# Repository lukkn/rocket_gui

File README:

# Communication between Teensy and MOTE board

## SETUP INSTRUNCTIONS
1. Connect each MoTE board used to 12V power, connecting to the 2 pins on J1 closest to the top of the board. Upper pin is power, lower pin is ground. Connect each teensy to the router via ethernet, and connect the control console to the same router
2. In the file "Example SD card Root/sensor_min_test.csv", add all necessary sensors and/or actuators, make sure to specify mote number, pin number, and sensor type (see below for sensor types). For ADCs, the pin number is weird. The first digit is the ADC number (counting from the left, starting at 0), and the second digit is the pin number. E.g. ADC pin number 11 is J20, pin 1. For 2ch ADCs, use a pin number of 0 for the left two pins and pin number 1 for the right two pins.
3. Once the teensy is powered and conneted, run gui.py, the orange status light on the teensy will be on if there is a connection. If you need to change any config informaiton, REBOOT THE TEENSY!!

## Sensor Types
* Teensy ADC
* i2c ADC 1ch
* i2c ADC 2ch
* servoPWM
* servoPWM_12V
* Binary GPIO

## Identifying each Teensy and MOTE Board

Each MOTE board will hold a teensy. We can identify each by their unique MOTE number.

They will be last digit of each MOTE's static IP. That digit will be saved as an ascii-value in MoteNumber.txt in SD card.

## Communication Protocol

Protocol used between Teensy and the GUI will be done in **UDP**.

## Types of Functions

There are 4 types of read functions for sensors and 2 types of write functions for actuators.

Each function is assigned an Interface Type Number.

**Read functions:**

1. Teensy ADC
2. i2c ADC 1 channel (ads122c4)
3. i2c ADC 2 channel (ads122c4) (for thermocouple)
4. flowmeter counter

**Write functions:**

5. servo PWM
6. binary gpio

| Operation | Interface Type Number | Sensor/Actuator                                 |
| --------- | --------------------- | ----------------------------------------------- |
| READ      | 1                     | Teensy ADC                                      |
| READ      | 2                     | I2C ADC 1 channel (ads122c4)                    |
| READ      | 3                     | I2C ADC 2 channel (ads122c4) (for thermocouple) |
| READ      | 4                     | Flowmeter Counter                               |
| WRITE     | 5                     | Servo PWM                                       |
| WRITE     | 6                     | Binary GPIO                                     |

## Packet Data Structure

Each packet will be sent and received as a **byte array**.

### Sensor Config Commands (Server -> Teensy):

**Byte Array**

| Byte 1  | Byte 2      |
| ------- | ----------- |
| pin_num | config_byte |

**Bit Array of `config_byte`**

| Bit 1 (MSB)                                                              | Bit 2                                              | Bit 3 - 8             |
| ------------------------------------------------------------------------ | -------------------------------------------------- | --------------------- |
| actuator write command = 0 (since this is not an actuator write command) | actuator state (not used in sensor config packets) | Interface Type Number |

**NB 1.** Byte variable can be of type `char` or `uint8` or `hex` as its eight bits long.

**NB 2.** Given we are dealing with sensors, _Interface Type Number_ is either 1, 2, or 3, and _Bit 1_ and _Bit 2_ are 0.

**NB 3.** Knowing the pin number and sensor type is enough info to call the correct sensor read function, which takes pin number as argument.

### Actuator Write Commands (Server -> Teensy):

**Byte Array**

| Byte 1  | Byte 2      |
| ------- | ----------- |
| pin_num | config_byte |

**Bit Array of `config_byte`**

| Bit 1 (MSB)                                                            | Bit 2          | Bit 3 - 8             |
| ---------------------------------------------------------------------- | -------------- | --------------------- |
| Actuator write command = 1 (because this is an actuator write command) | actuator state | Interface Type Number |

**NB 4.** Given we are dealing with actuators, _Interface Type Number_ is either 4 or 5.

### Sensor Data (Teensy -> Server)

The byte array ar however many sensors there are in each teensy, whose information is provided in config file

Each Teensy will send to the server a differently lengthed byte array.

**Byte Array**

| Byte 1              | Byte 2-5               | Byte 6              | Byte 7-10              | etc. (5 bytes per sensor: 1 pin byte, 4 data bytes) |
| ------------------- | ---------------------- | ------------------- | ---------------------- | --------------------------------------------------- |
| pin_num of sensor_1 | data_value of sensor_1 | pin_num of sensor_2 | data_value of sensor_2 | Pin & dava_val of sensors_3-to-n                    |

**NB 5.** _data_value_ for each sensor is an int (4 bytes).

# To compile Teensy code from command line (without Arduino IDE). NOT USED FOR CURRENT CODE

If cloning this repo to compile firmware, you need to run the following once (to download the teensy4 core):

```
git submodule init
git submodule update
```

To update submodules:

```
git submodule foreach git pull

dependencies:
arm-none-eabi-newlib
arm-none-eabi-gcc
```

The PWMServo library is modified to INVERT the PWM duty cycle because we're using a MOSFET to drive a higher voltage, which inverts the signal
line 198 of PMWServo.cpp

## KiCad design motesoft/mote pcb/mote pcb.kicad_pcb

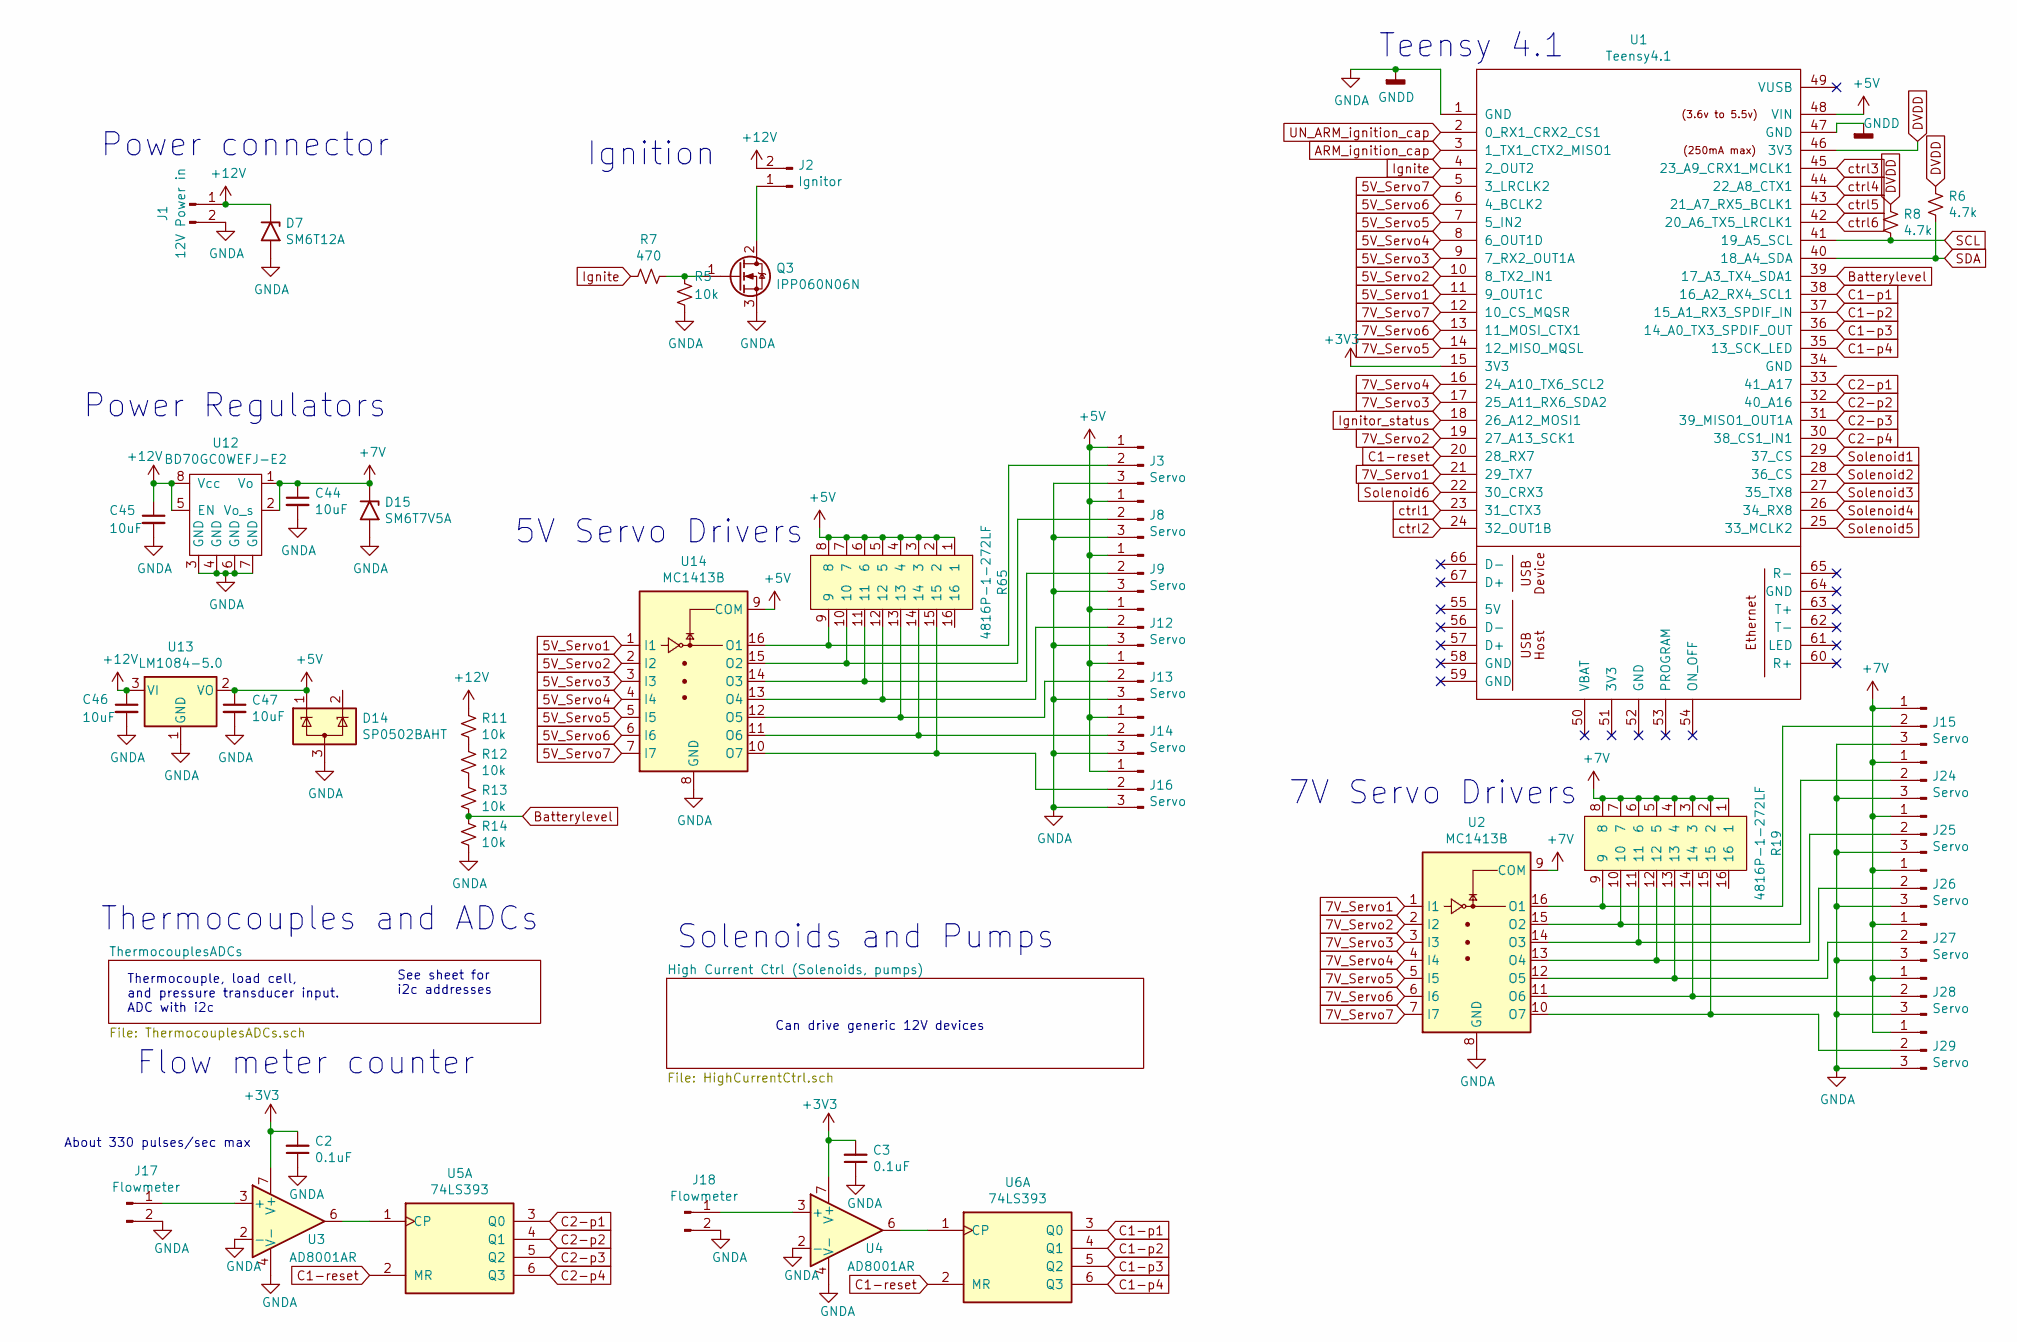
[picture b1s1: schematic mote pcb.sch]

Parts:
C2, C3: 0.1uF; C_0603_1608Metric_Pad1.08x0.95mm_HandSolder; LCSC Part # C14663
C44, C45, C46, C47: 10uF; C_0603_1608Metric_Pad1.08x0.95mm_HandSolder; LCSC Part # C19702
D7: SM6T12A; D_SMB
D14: SP0502BAHT; SOT-23
D15: SM6T7V5A; D_SMB
J1: 12V Power in; JST_EH_B4B-EH-A_1x04_P2.50mm_Vertical
J2: Ignitor; JST_EH_B4B-EH-A_1x04_P2.50mm_Vertical
J3, J8, J9, J12, J13, J14, J15, J16, J24, J25, J26, J27, J28, J29: Servo; JST_EH_B4B-EH-A_1x04_P2.50mm_Vertical
J17, J18: Flowmeter; JST_EH_B4B-EH-A_1x04_P2.50mm_Vertical
Q3: IPP060N06N; TO-220-3_Vertical
R5, R11, R12, R13, R14: 10k; R_0603_1608Metric_Pad0.98x0.95mm_HandSolder; LCSC Part # C25804
R6, R8: 4.7k; R_0603_1608Metric_Pad0.98x0.95mm_HandSolder; LCSC Part # C23162
R7: 470; R_0603_1608Metric_Pad0.98x0.95mm_HandSolder; LCSC Part # C23179
R19, R65: 4816P-1-272LF; SOIC-16W_5.3x10.2mm_P1.27mm
U1: Teensy4.1; Teensy41
U2, U14: MC1413B; SOIC-16_3.9x9.9mm_P1.27mm
U3, U4: AD8001AR; SOIC-8_3.9x4.9mm_P1.27mm
U5, U6: 74LS393; SOIC-14_3.9x8.7mm_P1.27mm
U12: BD70GC0WEFJ-E2; SOIC-8-1EP_3.9x4.9mm_P1.27mm_EP2.29x3mm_ThermalVias
U13: LM1084-5.0; TO-263-3_TabPin2

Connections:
5V_Servo1: U1.11 (9_OUT1C), U14.1 (I1)
5V_Servo2: U1.10 (8_TX2_IN1), U14.2 (I2)
5V_Servo3: U1.9 (7_RX2_OUT1A), U14.3 (I3)
5V_Servo4: U1.8 (6_OUT1D), U14.4 (I4)
5V_Servo5: U1.7 (5_IN2), U14.5 (I5)
5V_Servo6: U1.6 (4_BCLK2), U14.6 (I6)
5V_Servo7: U1.5 (3_LRCLK2), U14.7 (I7)
7V_Servo1: U1.21 (29_TX7), U2.1 (I1)
7V_Servo2: U1.19 (27_A13_SCK1), U2.2 (I2)
7V_Servo3: U1.17 (25_A11_RX6_SDA2), U2.3 (I3)
7V_Servo4: U1.16 (24_A10_TX6_SCL2), U2.4 (I4)
7V_Servo5: U1.14 (12_MISO_MQSL), U2.5 (I5)
7V_Servo6: U1.13 (11_MOSI_CTX1), U2.6 (I6)
7V_Servo7: U1.12 (10_CS_MQSR), U2.7 (I7)
+3V3: C2.2, C3.2, U1.15 (3V3), U3.7 (V+), U4.7 (V+); also elsewhere on the board
+5V: C47.1, D14.1 (K), J3.1, J8.1, J9.1, J12.1, J13.1, J14.1, J16.1, R65.1, R65.2, R65.3, R65.4, R65.5, R65.6, R65.7, R65.8, U1.48 (VIN), U13.2 (VO), U14.9 (COM)
+7.5V: C44.1, D15.1 (A1), J15.1, J24.1, J25.1, J26.1, J27.1, J28.1, J29.1, R19.1, R19.2, R19.3, R19.4, R19.5, R19.6, R19.7, R19.8, U2.9 (COM), U12.1 (Vo), U12.2 (Vo_s)
+12V: C45.1, C46.1, D7.1 (A1), J1.1, J2.2, R11.1, U12.5 (EN), U12.8 (Vcc), U13.3 (VI); also elsewhere on the board
Batterylevel: R13.2, R14.1, U1.39 (17_A3_TX4_SDA1)
C1-p1: U1.38 (16_A2_RX4_SCL1), U6.3 (Q0)
C1-p2: U1.37 (15_A1_RX3_SPDIF_IN), U6.4 (Q1)
C1-p3: U1.36 (14_A0_TX3_SPDIF_OUT), U6.5 (Q2)
C1-p4: U1.35 (13_SCK_LED), U6.6 (Q3)
C1-reset: U1.20 (28_RX7), U5.2 (MR), U6.2 (MR)
C2-p1: U1.33 (41_A17), U5.3 (Q0)
C2-p2: U1.32 (40_A16), U5.4 (Q1)
C2-p3: U1.31 (39_MISO1_OUT1A), U5.5 (Q2)
C2-p4: U1.30 (38_CS1_IN1), U5.6 (Q3)
DVDD: R6.1, R8.1, U1.46 (3V3)
GNDA: C2.1, C3.1, C44.2, C45.2, C46.2, C47.2, D7.2 (A2), D14.3 (A), D15.2 (A2), J1.2, J3.3, J8.3, J9.3, J12.3, J13.3, J14.3, J15.3, J16.3, J17.2, J18.2, J24.3, J25.3, J26.3, J27.3, J28.3, J29.3, Q3.3 (S), R5.2, R14.2, U1.1 (GND), U1.47 (GND), U2.8 (GND), U3.2 (-), U3.4 (V-), U4.2 (-), U4.4 (V-), U12.3 (GND), U12.4 (GND), U12.6 (GND), U12.7 (GND), U13.1 (GND), U14.8 (GND); also elsewhere on the board
Ignite: R7.2, U1.4 (2_OUT2)
unnamed: J2.1, Q3.2 (D)
unnamed: J3.2, R65.9, U14.16 (O1)
unnamed: J8.2, R65.10, U14.15 (O2)
unnamed: J9.2, R65.11, U14.14 (O3)
unnamed: J12.2, R65.12, U14.13 (O4)
unnamed: J13.2, R65.13, U14.12 (O5)
unnamed: J14.2, R65.14, U14.11 (O6)
unnamed: J15.2, R19.9, U2.16 (O1)
unnamed: J16.2, R65.15, U14.10 (O7)
unnamed: J17.1, U3.3 (+)
unnamed: J18.1, U4.3 (+)
unnamed: J24.2, R19.10, U2.15 (O2)
unnamed: J25.2, R19.11, U2.14 (O3)
unnamed: J26.2, R19.12, U2.13 (O4)
unnamed: J27.2, R19.13, U2.12 (O5)
unnamed: J28.2, R19.14, U2.11 (O6)
unnamed: J29.2, R19.15, U2.10 (O7)
unnamed: Q3.1 (G), R5.1, R7.1
unnamed: R11.2, R12.1
unnamed: R12.2, R13.1
unnamed: U3.6, U5.1 (CP)
unnamed: U4.6, U6.1 (CP)
SCL: R8.2, U1.41 (19_A5_SCL); also elsewhere on the board
SDA: R6.2, U1.40 (18_A4_SDA); also elsewhere on the board
Solenoid1: U1.29 (37_CS); also elsewhere on the board
Solenoid2: U1.28 (36_CS); also elsewhere on the board
Solenoid3: U1.27 (35_TX8); also elsewhere on the board
Solenoid4: U1.26 (34_RX8); also elsewhere on the board
Solenoid5: U1.25 (33_MCLK2); also elsewhere on the board
Solenoid6: U1.22 (30_CRX3); also elsewhere on the board
ctrl1: U1.23 (31_CTX3); also elsewhere on the board
ctrl2: U1.24 (32_OUT1B); also elsewhere on the board
ctrl3: U1.45 (23_A9_CRX1_MCLK1); also elsewhere on the board
ctrl4: U1.44 (22_A8_CTX1); also elsewhere on the board
ctrl5: U1.43 (21_A7_RX5_BCLK1); also elsewhere on the board
ctrl6: U1.42 (20_A6_TX5_LRCLK1); also elsewhere on the board

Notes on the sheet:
Thermocouple, load cell, and pressure transducer input. ADC with i2c
See sheet for i2c addresses
Ignition
Thermocouples and ADCs
Flow meter counter
Teensy 4.1
About 330 pulses/sec max
Power connector
7V Servo Drivers
Can drive generic 12V devices
Solenoids and Pumps
5V Servo Drivers
Power Regulators

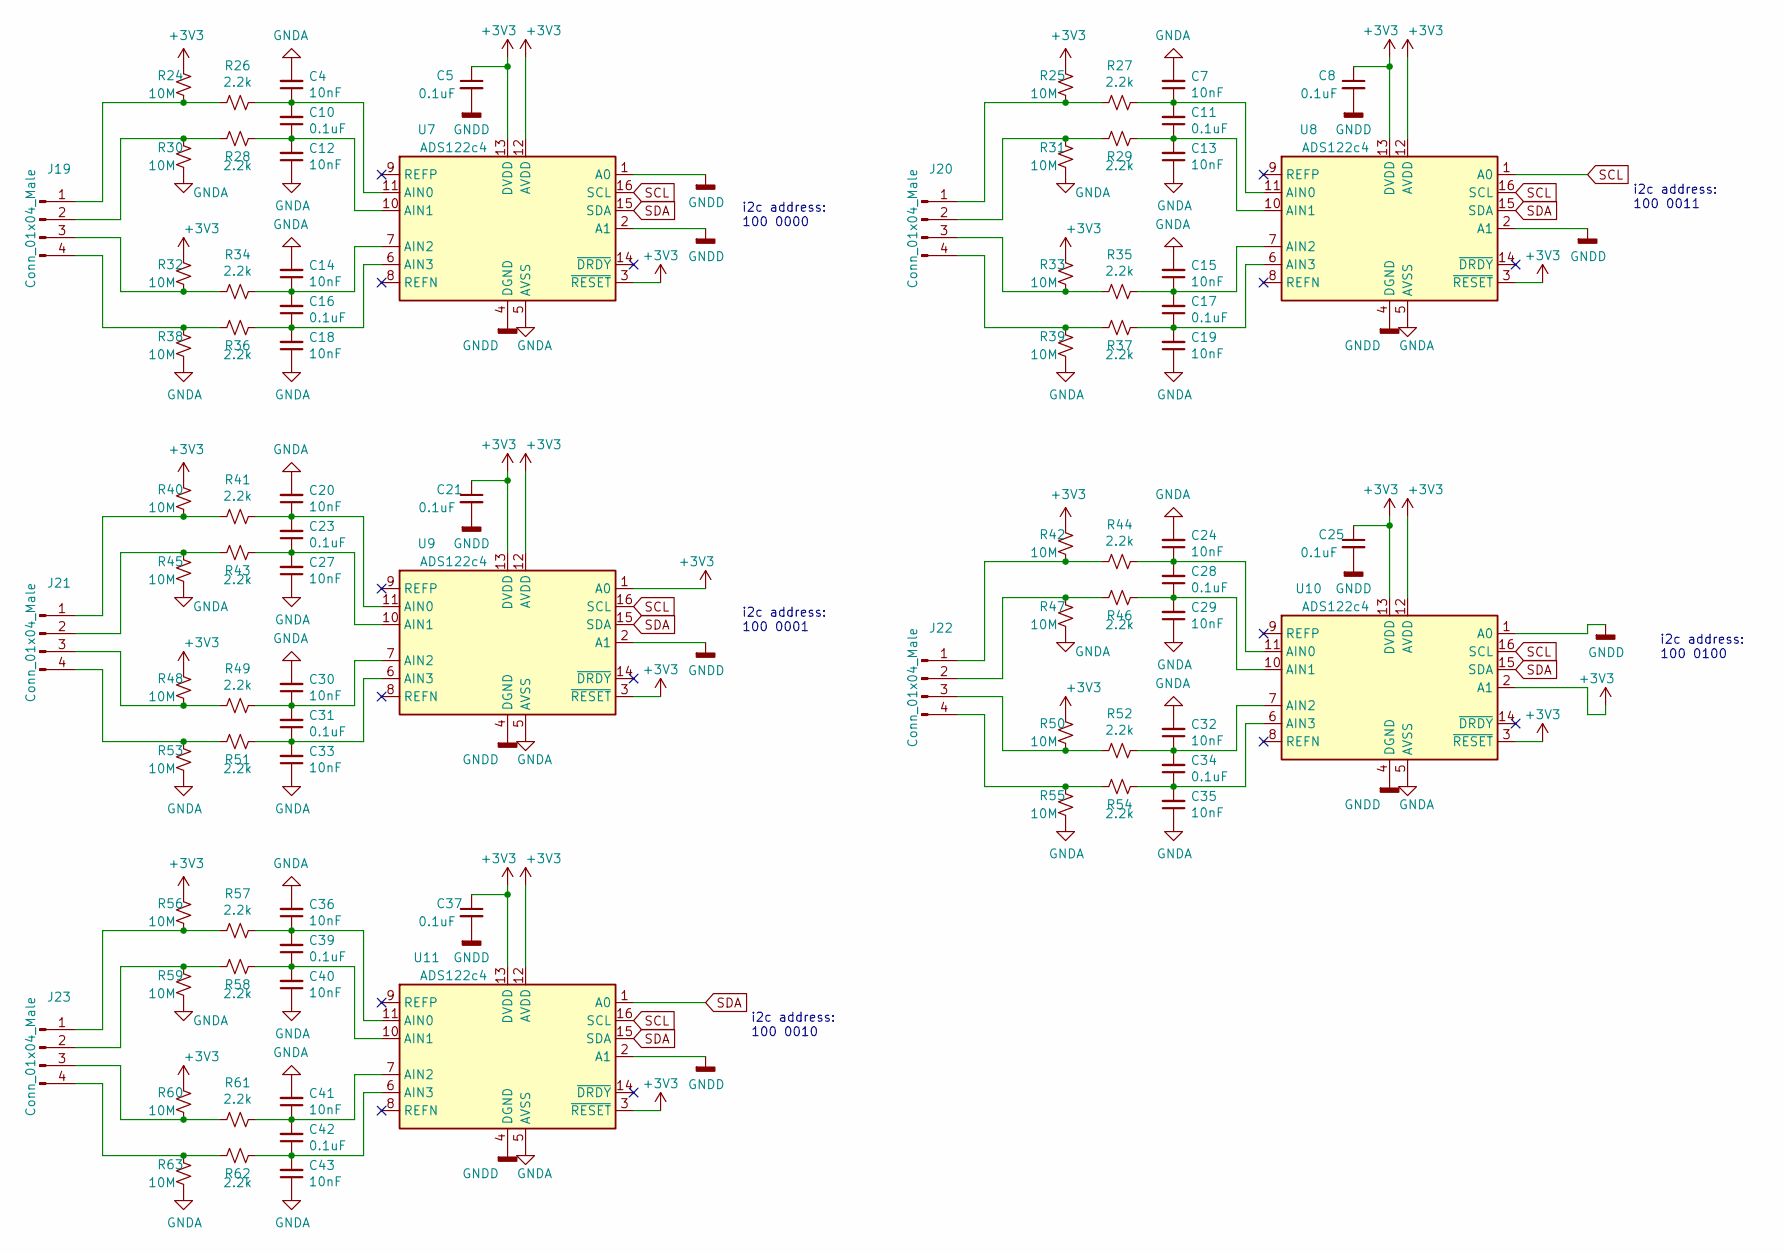
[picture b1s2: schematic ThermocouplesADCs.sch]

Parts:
C4, C7, C12, C13, C14, C15, C18, C19, C20, C24, C27, C29, C30, C32, C33, C35, C36, C40, C41, C43: 10nF; C_0603_1608Metric_Pad1.08x0.95mm_HandSolder; LCSC Part # C57112
C5, C8, C10, C11, C16, C17, C21, C23, C25, C28, C31, C34, C37, C39, C42: 0.1uF; C_0603_1608Metric_Pad1.08x0.95mm_HandSolder; LCSC Part # C14663
J19, J20, J21, J22, J23: Conn_01x04_Male; JST_EH_B4B-EH-A_1x04_P2.50mm_Vertical
R24, R25, R30, R31, R32, R33, R38, R39, R40, R42, R45, R47, R48, R50, R53, R55, R56, R59, R60, R63: 10M; R_0603_1608Metric_Pad0.98x0.95mm_HandSolder; LCSC Part # C7250
R26, R27, R28, R29, R34, R35, R36, R37, R41, R43, R44, R46, R49, R51, R52, R54, R57, R58, R61, R62: 2.2k; R_0603_1608Metric_Pad0.98x0.95mm_HandSolder; LCSC Part # C4190
U7, U8, U9, U10, U11: ADS122c4; TSSOP-16_4.4x5mm_P0.65mm

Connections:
+3V3: C5.1, C8.1, C21.1, C25.1, C37.1, R24.2, R25.2, R32.2, R33.2, R40.2, R42.2, R48.2, R50.2, R56.2, R60.2, U7.3 (~RESET), U7.12 (AVDD), U7.13 (DVDD), U8.3 (~RESET), U8.12 (AVDD), U8.13 (DVDD), U9.1 (A0), U9.3 (~RESET), U9.12 (AVDD), U9.13 (DVDD), U10.2 (A1), U10.3 (~RESET), U10.12 (AVDD), U10.13 (DVDD), U11.3 (~RESET), U11.12 (AVDD), U11.13 (DVDD); also elsewhere on the board
GNDA: C4.2, C5.2, C7.2, C8.2, C12.1, C13.1, C14.2, C15.2, C18.1, C19.1, C20.2, C21.2, C24.2, C25.2, C27.1, C29.1, C30.2, C32.2, C33.1, C35.1, C36.2, C37.2, C40.1, C41.2, C43.1, R30.1, R31.1, R38.1, R39.1, R45.1, R47.1, R53.1, R55.1, R59.1, R63.1, U7.1 (A0), U7.2 (A1), U7.4 (DGND), U7.5 (AVSS), U8.2 (A1), U8.4 (DGND), U8.5 (AVSS), U9.2 (A1), U9.4 (DGND), U9.5 (AVSS), U10.1 (A0), U10.4 (DGND), U10.5 (AVSS), U11.2 (A1), U11.4 (DGND), U11.5 (AVSS); also elsewhere on the board
unnamed: C10.1, C12.2, R28.2, U7.10 (AIN1)
unnamed: C4.1, C10.2, R26.2, U7.11 (AIN0)
unnamed: C11.1, C13.2, R29.2, U8.10 (AIN1)
unnamed: C7.1, C11.2, R27.2, U8.11 (AIN0)
unnamed: C14.1, C16.2, R34.2, U7.7 (AIN2)
unnamed: C15.1, C17.2, R35.2, U8.7 (AIN2)
unnamed: C16.1, C18.2, R36.2, U7.6 (AIN3)
unnamed: C17.1, C19.2, R37.2, U8.6 (AIN3)
unnamed: C20.1, C23.2, R41.2, U9.11 (AIN0)
unnamed: C23.1, C27.2, R43.2, U9.10 (AIN1)
unnamed: C24.1, C28.2, R44.2, U10.11 (AIN0)
unnamed: C28.1, C29.2, R46.2, U10.10 (AIN1)
unnamed: C30.1, C31.2, R49.2, U9.7 (AIN2)
unnamed: C31.1, C33.2, R51.2, U9.6 (AIN3)
unnamed: C32.1, C34.2, R52.2, U10.7 (AIN2)
unnamed: C34.1, C35.2, R54.2, U10.6 (AIN3)
unnamed: C36.1, C39.2, R57.2, U11.11 (AIN0)
unnamed: C39.1, C40.2, R58.2, U11.10 (AIN1)
unnamed: C41.1, C42.2, R61.2, U11.7 (AIN2)
unnamed: C42.1, C43.2, R62.2, U11.6 (AIN3)
unnamed: J19.1, R24.1, R26.1
unnamed: J19.2, R28.1, R30.2
unnamed: J19.3, R32.1, R34.1
unnamed: J19.4, R36.1, R38.2
unnamed: J20.1, R25.1, R27.1
unnamed: J20.2, R29.1, R31.2
unnamed: J20.3, R33.1, R35.1
unnamed: J20.4, R37.1, R39.2
unnamed: J21.1, R40.1, R41.1
unnamed: J21.2, R43.1, R45.2
unnamed: J21.3, R48.1, R49.1
unnamed: J21.4, R51.1, R53.2
unnamed: J22.1, R42.1, R44.1
unnamed: J22.2, R46.1, R47.2
unnamed: J22.3, R50.1, R52.1
unnamed: J22.4, R54.1, R55.2
unnamed: J23.1, R56.1, R57.1
unnamed: J23.2, R58.1, R59.2
unnamed: J23.3, R60.1, R61.1
unnamed: J23.4, R62.1, R63.2
SCL: U7.16 (SCL), U8.1 (A0), U8.16 (SCL), U9.16 (SCL), U10.16 (SCL), U11.16 (SCL); also elsewhere on the board
SDA: U7.15 (SDA), U8.15 (SDA), U9.15 (SDA), U10.15 (SDA), U11.1 (A0), U11.15 (SDA); also elsewhere on the board

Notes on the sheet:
i2c address: 100 0000
i2c address: 100 0001
i2c address: 100 0010
i2c address: 100 0011
i2c address: 100 0100

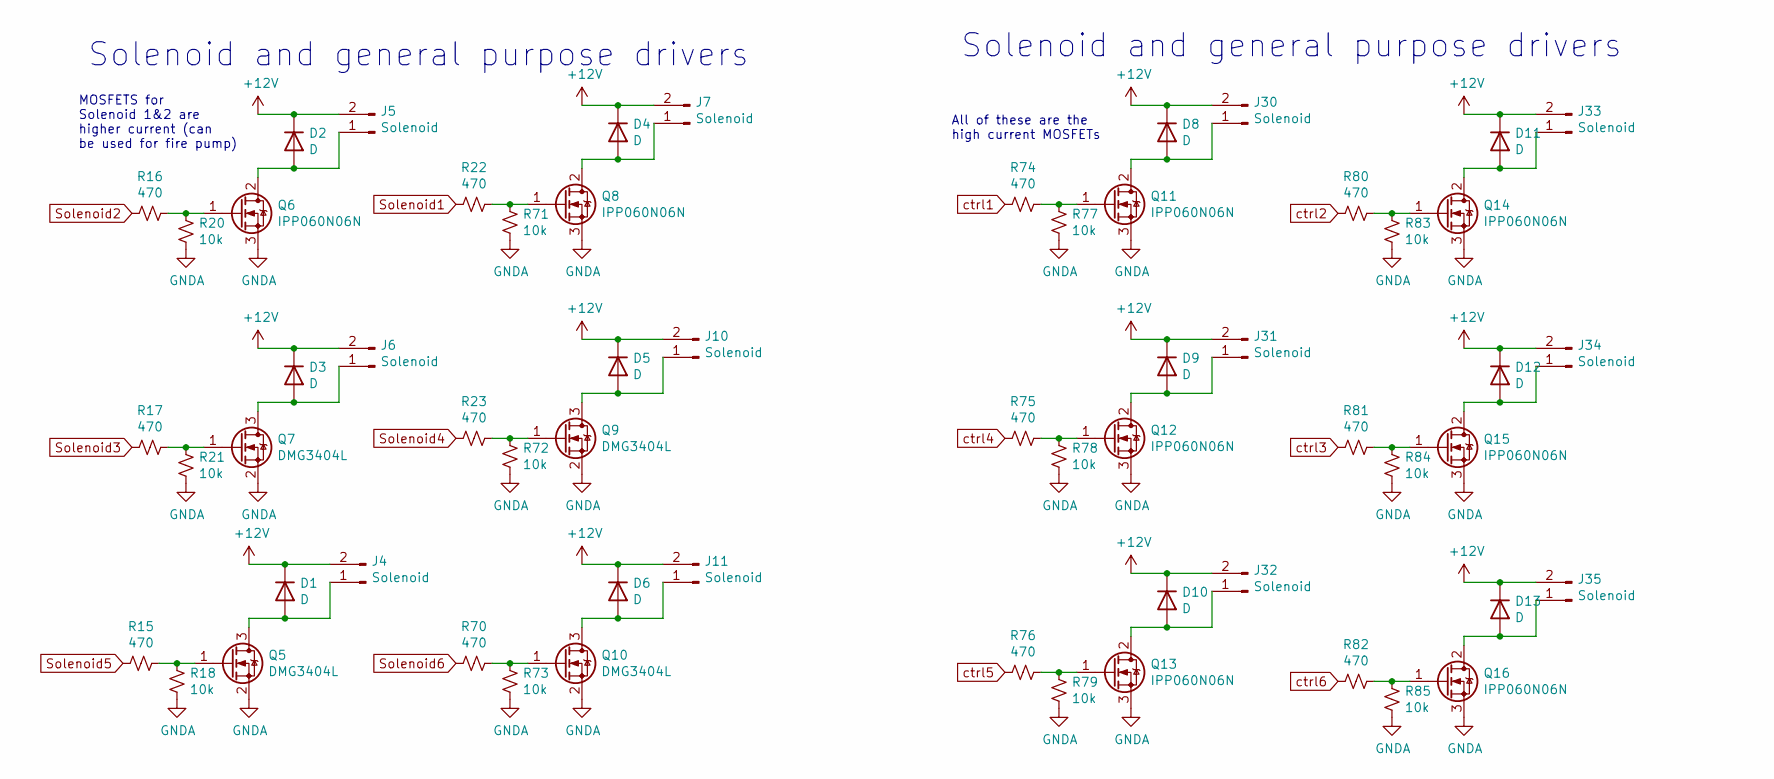
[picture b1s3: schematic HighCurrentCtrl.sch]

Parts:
D1, D2, D3, D4, D5, D6, D8, D9, D10, D11, D12, D13: D; D_SOD-123; LCSC Part # C8598
J4, J5, J6, J7, J10, J11, J30, J31, J32, J33, J34, J35: Solenoid; JST_EH_B4B-EH-A_1x04_P2.50mm_Vertical
Q5, Q7, Q9, Q10: DMG3404L; SOT-23
Q6, Q8, Q11, Q12, Q13, Q14, Q15, Q16: IPP060N06N; TO-220-3_Vertical
R15, R16, R17, R22, R23, R70, R74, R75, R76, R80, R81, R82: 470; R_0603_1608Metric_Pad0.98x0.95mm_HandSolder; LCSC Part # C23179
R18, R20, R21, R71, R72, R73, R77, R78, R79, R83, R84, R85: 10k; R_0603_1608Metric_Pad0.98x0.95mm_HandSolder; LCSC Part # C25804

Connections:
+12V: D1.1 (K), D2.1 (K), D3.1 (K), D4.1 (K), D5.1 (K), D6.1 (K), D8.1 (K), D9.1 (K), D10.1 (K), D11.1 (K), D12.1 (K), D13.1 (K), J4.2, J5.2, J6.2, J7.2, J10.2, J11.2, J30.2, J31.2, J32.2, J33.2, J34.2, J35.2; also elsewhere on the board
GNDA: Q5.2 (S), Q6.3 (S), Q7.2 (S), Q8.3 (S), Q9.2 (S), Q10.2 (S), Q11.3 (S), Q12.3 (S), Q13.3 (S), Q14.3 (S), Q15.3 (S), Q16.3 (S), R18.2, R20.2, R21.2, R71.2, R72.2, R73.2, R77.2, R78.2, R79.2, R83.2, R84.2, R85.2; also elsewhere on the board
unnamed: D1.2 (A), J4.1, Q5.3 (D)
unnamed: D2.2 (A), J5.1, Q6.2 (D)
unnamed: D3.2 (A), J6.1, Q7.3 (D)
unnamed: D4.2 (A), J7.1, Q8.2 (D)
unnamed: D5.2 (A), J10.1, Q9.3 (D)
unnamed: D6.2 (A), J11.1, Q10.3 (D)
unnamed: D8.2 (A), J30.1, Q11.2 (D)
unnamed: D9.2 (A), J31.1, Q12.2 (D)
unnamed: D10.2 (A), J32.1, Q13.2 (D)
unnamed: D11.2 (A), J33.1, Q14.2 (D)
unnamed: D12.2 (A), J34.1, Q15.2 (D)
unnamed: D13.2 (A), J35.1, Q16.2 (D)
unnamed: Q5.1 (G), R15.1, R18.1
unnamed: Q6.1 (G), R16.1, R20.1
unnamed: Q7.1 (G), R17.1, R21.1
unnamed: Q8.1 (G), R22.1, R71.1
unnamed: Q9.1 (G), R23.1, R72.1
unnamed: Q10.1 (G), R70.1, R73.1
unnamed: Q11.1 (G), R74.1, R77.1
unnamed: Q12.1 (G), R75.1, R78.1
unnamed: Q13.1 (G), R76.1, R79.1
unnamed: Q14.1 (G), R80.1, R83.1
unnamed: Q15.1 (G), R81.1, R84.1
unnamed: Q16.1 (G), R82.1, R85.1
Solenoid1: R22.2; also elsewhere on the board
Solenoid2: R16.2; also elsewhere on the board
Solenoid3: R17.2; also elsewhere on the board
Solenoid4: R23.2; also elsewhere on the board
Solenoid5: R15.2; also elsewhere on the board
Solenoid6: R70.2; also elsewhere on the board
ctrl1: R74.2; also elsewhere on the board
ctrl2: R80.2; also elsewhere on the board
ctrl3: R81.2; also elsewhere on the board
ctrl4: R75.2; also elsewhere on the board
ctrl5: R76.2; also elsewhere on the board
ctrl6: R82.2; also elsewhere on the board

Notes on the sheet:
MOSFETS for Solenoid 1&2 are higher current (can be used for fire pump)
Solenoid and general purpose drivers
All of these are the high current MOSFETs

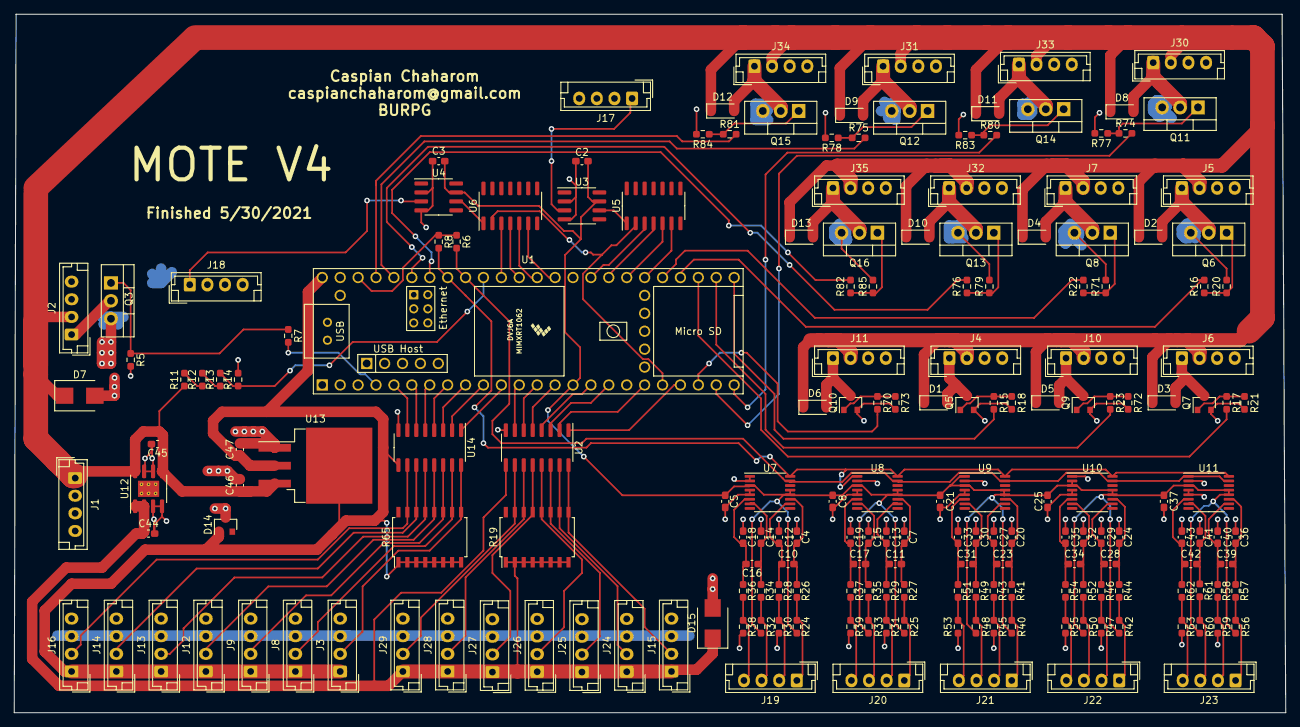
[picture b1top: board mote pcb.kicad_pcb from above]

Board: 2 copper layers, 180.3 x 99.1 mm, 192 parts (0 on the bottom side), 131 nets.

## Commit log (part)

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2023-12-26 requirements and folder refactor
2023-12-27 flask gui
2023-12-27 code cleanup
2023-12-27 button attempt
2023-12-27 better buttons
2023-12-27 button shit
2023-12-27 Placed buttons inside container
    - cleaned up repeated code
2023-12-27 update names
2023-12-27 Revert "better buttons"
    This reverts commit 9b7cf012b878d2701775844e0bdb4d0b0a95b217.
2023-12-27 Made buttons unselectable
    *spackle* sparkle
2023-12-27 Fixed unable to submit coordinates
    file was opened as read only
2023-12-27 fixed on/off buttons
    -changed buttons to div
2023-12-27 smaller buttons for actuators
2023-12-27 implemented collapsible menu
2023-12-27 Updated menu
2023-12-27 25px offset for menu bar and button status
2023-12-27 all actuators turned off on page load, other small changes
2023-12-27 button config almost correct overlay
2023-12-28 Made toggle buttons
    ... that I now have to remove
2023-12-28 Resolved conflicts
2023-12-28 Updated buttons to not toggle :(
2023-12-28 deleted useless files
2023-12-28 starting websocket conversion, much to do
2023-12-28 example web socket recieve shit
2023-12-28 example flask websocket
2023-12-28 Created sensor page that receives data from socket
2023-12-28 moved over to websocket for actuators.html page, need websocket for / and /loadconfig
2023-12-28 really rough sensors page
2024-01-01 dictionary parsing for config file with checks
2024-01-01 dictionary parsing for sensors page and id update
2024-01-02 sensor tare response, standardize response, hardcoded config
2024-01-02 renamed global variable sensors to sensor_list to avoid conflicts with html get function 'sensors' when using hardcoded dummy data
2024-01-02 tare buttons
2024-01-02 Created live graph
2024-01-02 Updated data frequency and improved performance
2024-01-02 local library for Chart.js
2024-01-02 sensors page uses local lib for Chart.js
2024-01-02 loggs data and emits data at different frequencies
2024-01-03 sensors on p&id view page, seperate table style pages for sensors and actuators
2024-01-03 renamed p&idview to pidview
2024-01-03 part of renaming
2024-01-03 added arm/disarm button
2024-01-03 Added graph toggle
    - checkbox for each sensor, graph appears when checked
2024-01-03 work in progress
2024-01-04 work in progress on main page
2024-01-04 Resized graphs
2024-01-04 Updated sensor page layout
2024-01-04 new graphs please
2024-01-04 Fixed graph appearance
2024-01-05 created js native graph on loadconfig page
2024-01-05 custom graph testing
2024-01-05 Created makeChart library
2024-01-05 Added add empty chart functionality
2024-01-06 performance tests and websocket lag fixed
2024-01-06 two lines on a graph example
2024-01-07 button presses and states are processed server side and ping added
2024-01-08 Added file upload/submit messages
2024-01-08 ping and app startup behavior change
2024-01-08 arm/disarm button now uses sockets instead of POST, no longer sending timestamps
2024-01-08 minor changes since last commit
2024-01-08 Implemented charts that plot lines when checkbox checked
    - still needs y-axis scale
    - still needs labelled/colored lines
2024-01-08 Fixed data duplication bug
    - if two or more charts were plotting the same sensor data updates were done multiple times
2024-01-09 bug fixes
2024-01-09 sync sensors
2024-01-09 gpt code that might be useful for queue management in constant time
2024-01-09 added different line colors
2024-01-09 testing and small changes, timer added to sensors
2024-01-09 Added grid lines
2024-01-09 Fixed graph data alignment on x-axis
2024-01-09 graph testing
2024-01-09 removed redundant imports
2024-01-09 created doubly linked list class
2024-01-09 Updated data storage to linkedlist
2024-01-09 updated defineScale for better performance
2024-01-09 test data for linked list
2024-01-09 test data for 3rd trial with linked list
2024-01-09 4th test using normal list
2024-01-10 deleted obsolete Chart.js file
2024-01-10 Removed extraneous files
2024-01-10 Revert to array data storage
2024-01-11 Created autosequence page
    - displays submitted csv file
2024-01-11 Update autosequence page layout
2024-01-11 Update autosequence style
2024-01-11 data points is param of updateData function, more colors and colors rotate if all used, some var types changed to let or const types
2024-01-11 removed unused imports
2024-01-11 config button uploads config, sig figs updated on sensors page and graphs
2024-01-11 Implemented autosequence backend and response
2024-01-12 Added stop timer function
2024-01-12 Updated launch to check for config, added cancel response
2024-01-12 Prevent relaunching after cancel without reuploading file
2024-01-12 minor changes
2024-01-13 renamed received_actuator_button_press socket to received_button_press
2024-01-13 dependencies in project folder, standardization of variable names, comments
    flask and flask-socketio are added into a folder. now a computer only needs python to run this gui
2024-01-13 updated .gitignore file
2024-01-13 deleted pycache
2024-01-14 production server eventlet used
2024-01-18 added autosequence page button to start page
2024-01-19 changed port to 5001 so it might work with macOS
2024-01-30 require gtk3
2024-01-30 require gtk3 sensor_logging
2024-01-30 Sensor_logging require gtk3
2024-01-30 Fixed bug where directory did not exist
2024-02-07 networking reqs
2024-02-09 Created networking skeleton
2024-02-09 rolled back python_flask_and_flaskio_and_eventlet_libraries folder
2024-02-09 Fixed networking errors
2024-02-09 autoseq actuators synced with other pages, boolean value in python prevents double clicks of launch button, pages update sensors+actuators on config upload, when disarmed sensor buttons can be clicke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
2024-02-09 send actuators commands to mote on button press
2024-02-09 minor import changes
2024-02-09 small import changes
2024-02-09 copy of socket at this moment
2024-02-09 changed 'button' to 'actuator'
2024-02-09 .gitignore update
2024-02-10 removed __pycache__ files
2024-02-10 .gitignore with every __pycache__
2024-02-10 autoseq changes and server change
2024-02-11 Style changes on home page (WIP)
2024-02-11 added telemetry receiver
2024-02-11 library and autoseq changes
2024-02-11 autoseq timing changes
2024-02-11 updated redline file
2024-02-11 tims changes
2024-02-11 added sensor data example
2024-02-12 new config and TODO
2024-02-12 slightly poked code
2024-02-12 Updated home page
2024-02-12 parse sensor data into frontend
2024-02-12 amended sensor data parsing
2024-02-12 fixed mote id in sensor telemetry
2024-02-13 modified MoTE firmware
2024-02-13 modified so we don't need sd card, reads as MoTE1
2024-02-13 dummy name for the real main.cpp
2024-02-13 completed telemetry sensor data integration into graph
2024-02-16 updated homepage appearance
2024-02-19 Generalized autosequence functions
2024-02-19 configs and lora mote
2024-02-19 updated .gitignore
2024-02-20 Implemented abort sequence
2024-02-20 updated abort sequence
    - check autosequence is running before abort or cancel
    - check abort sequence uploaded before launch
2024-02-20 gui pings mote
2024-02-20 implemented ping and connection status
2024-02-21 socket issues
2024-02-21 lora config and networking takes signed ints now
2024-02-21 some ping stuff for windows
2024-02-21 main.cpp in motesoft is actual mote firmware
2024-02-22 updated index page
    - check config file format
    - appearance update
2024-02-22 updated index page
2024-02-23 sample autoseq file
2024-02-25 added 'unit' for config file and pythonping stuff
2024-02-25 changed name to avoid circular import err
2024-02-26 implemented tare and untare
2024-02-26 removed unused files
2024-02-26 not using local python libs any more
2024-02-26 deleted this file. plz also delete on local git
2024-02-26 implemented unit conversion
2024-02-26 finished ping
2024-02-26 renamed folder with libraries and updated .gitignore
2024-02-26 custom libs will be used over normally installed libs
2024-02-26 removed some duplicates in .gitignore
2024-02-26 enforce custom imports for both files, could be helpful on some systems
2024-02-26 implemented sensor logging
2024-02-26 Updated sensor logging to generate new filenames
2024-02-27 Autosequence page update and fixed taring
2024-02-27 Sensor logging without slowdown
2024-02-27 Implemented actuator acknowledgement
    + actuators page update
2024-02-28 deleted __pycache__ folders and updated .gitignore
2024-02-28 execute_abort_sequence now uses the same (more accurate) timing method as execute_autosequence, as opposed to delays which drift by +- 50msec
2024-02-28 new ping that works on linux; all threads start on launch and handle all states; removed 'guion' socket emit from index.html as it did nothing; connect status is packet based instead of ping based
2024-02-28 Implemented redline upload
2024-02-29 implemented actuator logging (on change)
    - logging based on actuator acknowledgement, if same button is clicked multiple times it logs multiple times
2024-02-29 Updated sensor page appearance
2024-03-01 Updated status bar for each page
    - added connection status
    - added system time
    - added arm/disarm button
2024-03-02 Fixed autosequence bug and added watermark
2024-03-06 Tim's changes
2024-03-07 Update auto/abort sequence execution code design
2024-03-07 Config changes
2024-03-07 updated sensor and actuator logs naming
2024-03-07 Fixed sensor graph sizing bug
2024-03-08 fixed horizontal scrolling on actuators and home page
2024-03-08 Fixed overlaping pin numbers
2024-03-11 Added redline toggle switch
2024-03-12 Added redline skeleton logic
    - maintain moving window of recent data
    - emit abort if limit exceeded
    - limit checking NOT implemented
2024-03-12 Implemented redline threshold display on sensor graphs
    - only displays when relevant sensors checked
    - only displays when datapoints close to threshold
2024-03-12 Fixed sensor threshold display
    - increased range of graph to 10% above and below max and min data
    - added threshold line labels
2024-03-12 Fixed redline switch issues
    - fixed reversed colors
    - added labels in top of switches
2024-03-15 Updated system time display to hh:mm:ss
2024-03-15 Added redline on/off check
2024-03-15 Fixed redline switch not reflecting redline state
2024-03-15 Fixed sensor tare bug
2024-03-15 fixed sensor unit convert bug
2024-03-15 Added TTL for sensor data + updated sensor processing for efficiency
2024-03-15 Improved sensor data display + logging efficiency and fixed sensor packet polling bug
    - combined sensor logging and display processing/sending of data
2024-03-16 Fixed sensor timeout bugs
2024-03-16 Updated sensor logging format
2024-03-16 fixed actuator buttons on pidview, no acks yet
2024-03-16 working sensor data
2024-03-16 taring for pidview page
2024-03-16 tims changes + update sensor page to column layout
2024-03-16 added libs2 binaries to .gitignore
2024-03-22 fixed sensor table padding
2024-03-22 grey out actuators when disarmed/disconnected
2024-03-23 Enabled changing mote names on the gui
2024-03-23 Made home page buttons responsive
2024-03-23 Added display for mote config status
2024-03-23 catch ping error
2024-03-23 Caught heartbeat error and removed unused files
2024-03-23 logging both actuator button presses and acks
2024-03-23 Fixed invalid autosequence upload bug and logging timestamp bug
    - logs headers said ms but timestamps were in s
    - certain invalid autosequence files caused an error which prevented the alert from appearing
2024-03-25 Fixed actuator log naming bug
2024-03-26 Fixed sensor taring bug
2024-03-26 Fixed actuators click when mote disconnected bug
2024-03-26 Fixed castrated logo on sensors page
2024-03-26 Fixed sensor graphs resetting when adding new chart
2024-04-05 implemented act buttons init to On when unpowered state set to Open
2024-04-13 bunch of little changes + optimizations
2024-04-19 Updated sensor_offset files to include config file name
2024-04-19 Updated actuator buttons to be responsive
2024-05-26 small cleanup
